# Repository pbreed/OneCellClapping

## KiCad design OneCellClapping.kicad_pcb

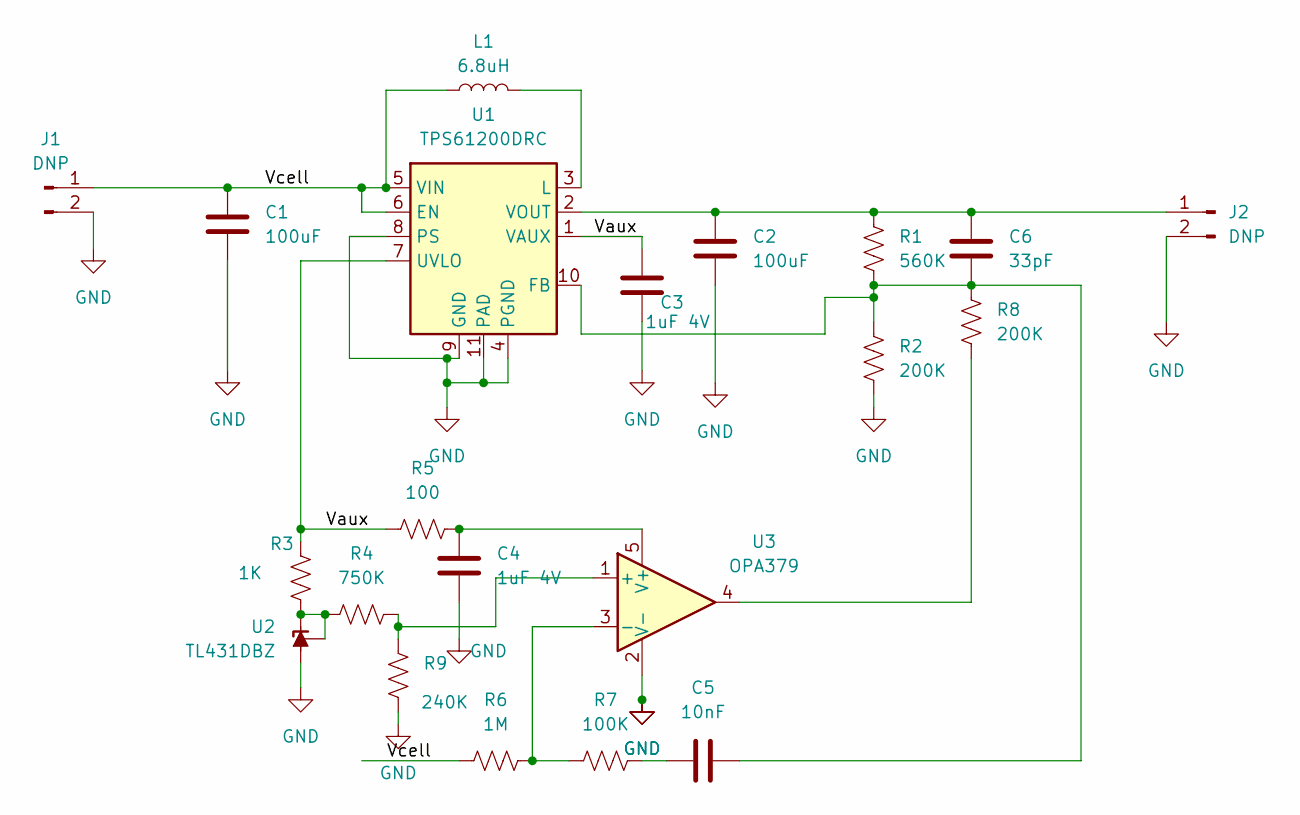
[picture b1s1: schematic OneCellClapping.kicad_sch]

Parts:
C1, C2: 100uF; C_1206_3216Metric
C3, C4: 1uF 4V; C_0402_1005Metric
C5: 10nF; C_0402_1005Metric
C6: 33pF; C_0402_1005Metric
J1, J2: DNP; PinHeader_1x02_P2.54mm_Vertical
L1: 6.8uH; IND_VLS252010HBX-6R8M-1; Part VLS252010HBX-6R8M-1; Digikey 587-3228-1-ND
R1: 560K; R_0402_1005Metric
R2, R8: 200K; R_0402_1005Metric
R3: 1K; R_0402_1005Metric
R4: 750K; R_0402_1005Metric
R5: 100; R_0402_1005Metric
R6: 1M; R_0402_1005Metric
R7: 100K; R_0402_1005Metric
R9: 240K; R_0402_1005Metric
U1: TPS61200DRC; Texas_S-PVSON-N10_ThermalVias
U2: TL431DBZ; SOT-23
U3: OPA379; SOT-353_SC-70-5

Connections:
/Vaux: C3.1, R3.1, R5.1, U1.1 (VAUX), U1.7 (UVLO)
/Vcell: C1.1, J1.1, L1.1, R6.1, U1.5 (VIN), U1.6 (EN)
GND: C1.2, C2.2, C3.2, C4.2, J1.2, J2.2, R2.2, R9.2, U1.4 (PGND), U1.8 (PS), U1.9 (GND), U1.11 (PAD), U2.3 (A), U3.2 (V-)
unnamed: C5.1, R7.2
unnamed: C2.1, C6.1, J2.1, R1.1, U1.2 (VOUT)
unnamed: R8.2, U3.4
unnamed: C5.2, C6.2, R1.2, R2.1, R8.1, U1.10 (FB)
unnamed: L1.2, U1.3 (L)
unnamed: R3.2, R4.1, U2.1 (K), U2.2 (REF)
unnamed: R4.2, R9.1, U3.1 (+)
unnamed: R6.2, R7.1, U3.3 (-)
unnamed: C4.1, R5.2, U3.5 (V+)

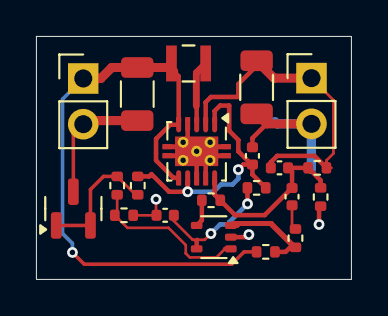
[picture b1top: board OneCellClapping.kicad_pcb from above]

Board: 2 copper layers, 17.5 x 13.5 mm, 21 parts (0 on the bottom side), 12 nets.
